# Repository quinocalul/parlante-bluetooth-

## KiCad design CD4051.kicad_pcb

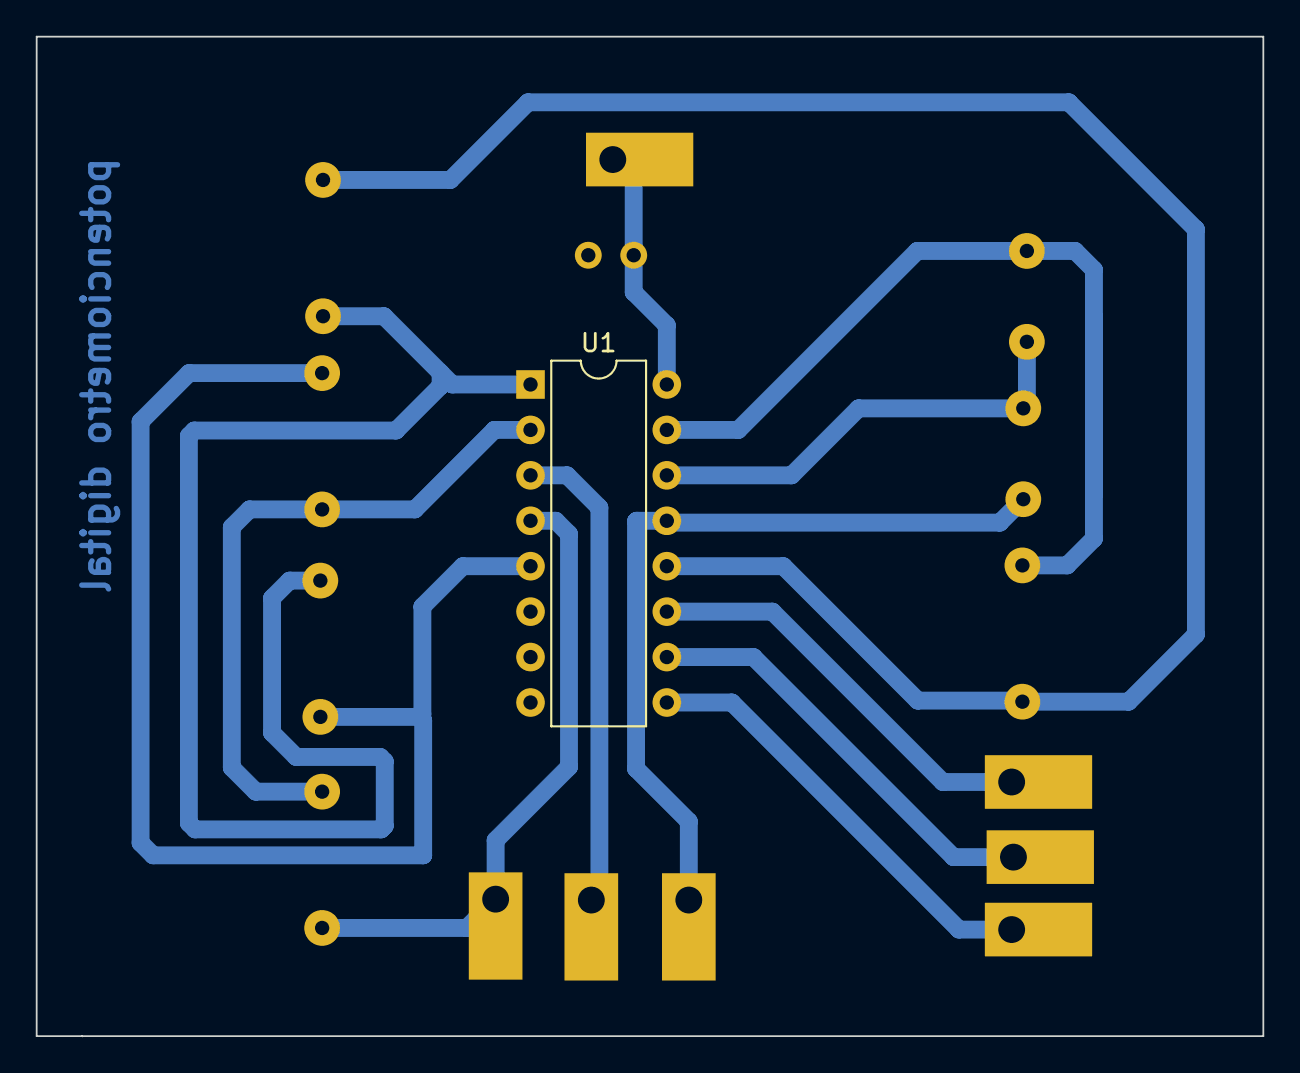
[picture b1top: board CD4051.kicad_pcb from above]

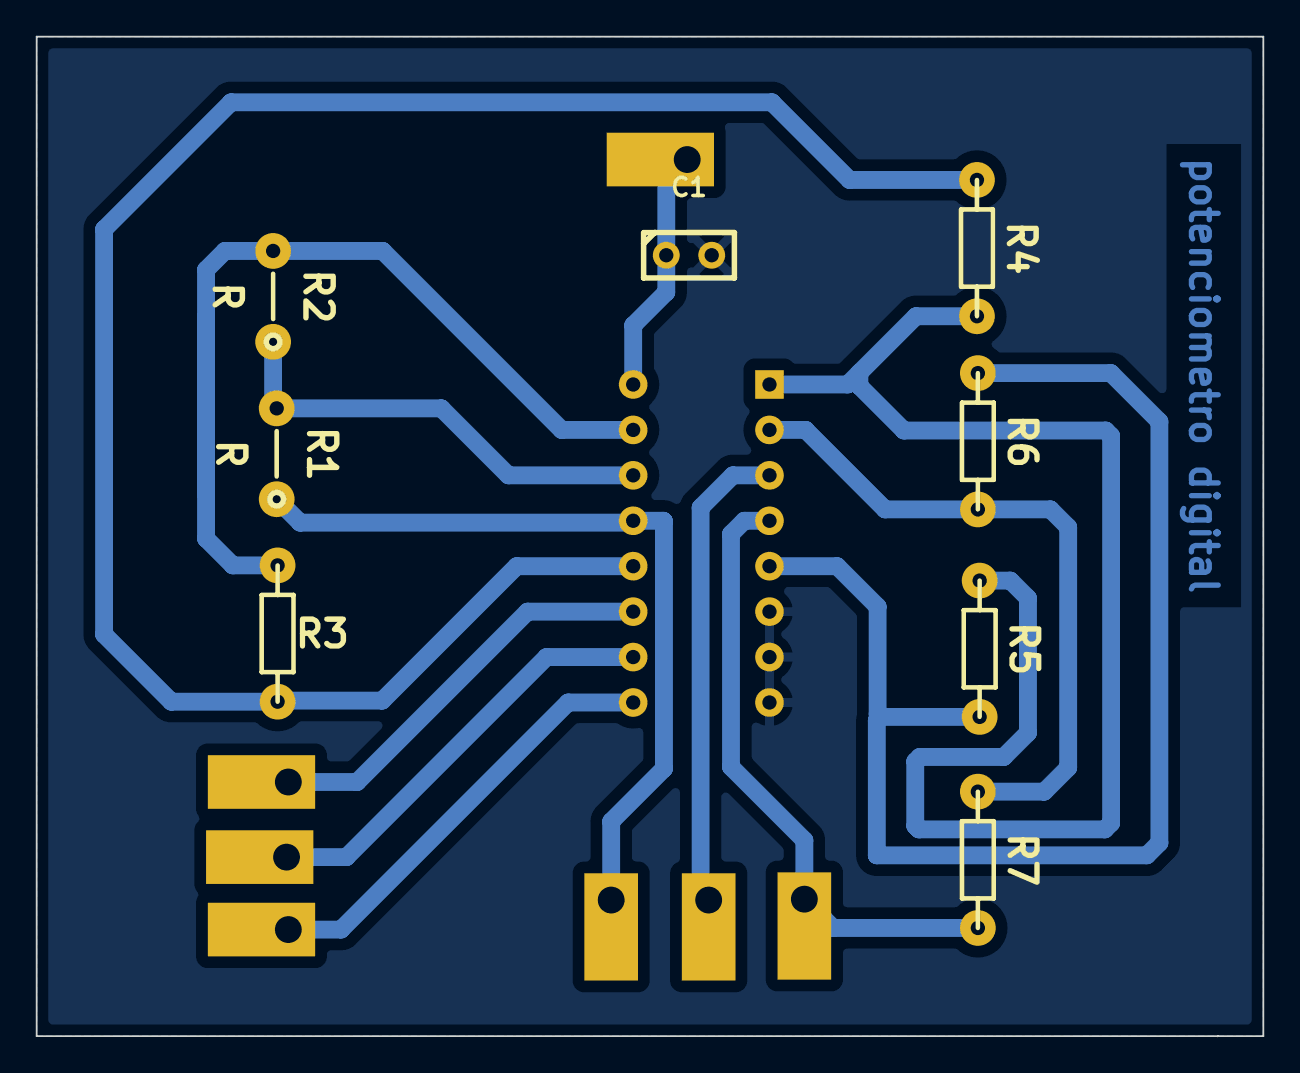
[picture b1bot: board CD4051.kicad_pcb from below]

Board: 2 copper layers, 68.6 x 55.9 mm, 16 parts (11 on the bottom side), 14 nets.

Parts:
C1: C; CAP_0.1
J1, J2, J3, J4, J5, J6, J7: Cable_PAD; Cable_1,5mm
R1, R2: R; RES0.2
R3, R4, R5, R6, R7: R; RES0.3
U1: CD4051B; DIP-16_W7.62mm

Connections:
GND: C1.2, U1.6 (INH), U1.7 (VEE), U1.8 (VSS)
unnamed: C1.1, J7.1, U1.16 (VDD)
unnamed: J1.1, R7.2, U1.4 (X7)
unnamed: J2.1, R1.1, U1.13 (X0)
unnamed: J3.1, U1.3 (X)
unnamed: J4.1, U1.10 (B)
unnamed: J5.1, U1.11 (A)
unnamed: J6.1, U1.9 (C)
unnamed: R1.2, R2.1, U1.14 (X1)
unnamed: R2.2, R3.1, U1.15 (X2)
unnamed: R3.2, R4.1, U1.12 (X3)
unnamed: R4.2, R5.1, U1.1 (X4)
unnamed: R5.2, R6.1, U1.5 (X5)
unnamed: R6.2, R7.1, U1.2 (X6)

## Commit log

2023-02-28 Create codigo parlante
